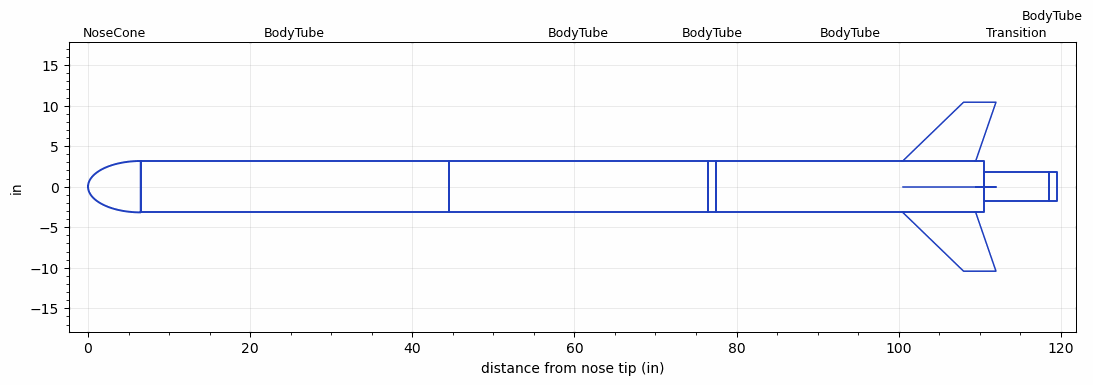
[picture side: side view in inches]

<RASAeroDocument>
 <FileVersion>2</FileVersion>
 <RocketDesign>
  <NoseCone>
   <Length>6.5</Length>
   <Diameter>6.34</Diameter>
   <Shape>Elliptical</Shape>
   <Location>0</Location>
  </NoseCone>
  <BodyTube>
   <Length>38</Length>
   <Diameter>6.34</Diameter>
   <Location>6.5</Location>
  </BodyTube>
  <BodyTube>
   <Length>32</Length>
   <Diameter>6.34</Diameter>
   <Location>44.5</Location>
  </BodyTube>
  <BodyTube>
   <Length>1</Length>
   <Diameter>6.34</Diameter>
   <Location>76.5</Location>
  </BodyTube>
  <BodyTube>
   <Length>33</Length>
   <Diameter>6.34</Diameter>
   <RailGuideDiameter>0.49</RailGuideDiameter>
   <RailGuideHeight>0.187</RailGuideHeight>
   <Location>77.5</Location>
   <Fin>
    <Count>4</Count>
    <Chord>9</Chord>
    <Span>7.25</Span>
    <SweepDistance>7.5</SweepDistance>
    <TipChord>4</TipChord>
    <Thickness>0.125</Thickness>
    <Location>10</Location>
    <AirfoilSection>Square</AirfoilSection>
   </Fin>
   <Protuberance>
    <StreamlinedNoBaseDrag>7</StreamlinedNoBaseDrag>
    <StreamlinedWithBaseDrag>0</StreamlinedWithBaseDrag>
    <InclinedPlate1Angle>0</InclinedPlate1Angle>
    <InclinedPlate1FrontalArea>0</InclinedPlate1FrontalArea>
    <InclinedPlate2Angle>0</InclinedPlate2Angle>
    <InclinedPlate2FrontalArea>0</InclinedPlate2FrontalArea>
   </Protuberance>
  </BodyTube>
  <Transition>
   <Length>8</Length>
   <Diameter>3.65</Diameter>
   <Location>110.5</Location>
   <RearDiameter>3.65</RearDiameter>
  </Transition>
  <BodyTube>
   <Length>1</Length>
   <Diameter>3.65</Diameter>
   <Location>118.5</Location>
  </BodyTube>
  <Surface>Rough Camouflage Paint</Surface>
  <ModifiedBarrowman>False</ModifiedBarrowman>
  <Turbulence>False</Turbulence>
  <UseBooster1>False</UseBooster1>
  <UseBooster2>False</UseBooster2>
 </RocketDesign>
 <LaunchSite>
  <Altitude>0</Altitude>
  <Pressure>0</Pressure>
  <RodAngle>10</RodAngle>
  <RodLength>10</RodLength>
  <Temperature>74</Temperature>
  <WindSpeed>20</WindSpeed>
 </LaunchSite>
 <Recovery>
  <Altitude1>1000</Altitude1>
  <Altitude2>800</Altitude2>
  <DeviceType1>Parachute</DeviceType1>
  <DeviceType2>Parachute</DeviceType2>
  <Event1>True</Event1>
  <Event2>True</Event2>
  <Size1>18</Size1>
  <Size2>96</Size2>
  <EventType1>Apogee</EventType1>
  <EventType2>Altitude</EventType2>
  <CD1>1.55</CD1>
  <CD2>2.2</CD2>
 </Recovery>
 <SimulationList>
  <Simulation>
   <SustainerEngine>L1390G  (AT)</SustainerEngine>
   <SustainerLaunchWt>42.3</SustainerLaunchWt>
   <SustainerNozzleDiameter>1</SustainerNozzleDiameter>
   <SustainerCG>71.85</SustainerCG>
   <SustainerIgnitionDelay>0</SustainerIgnitionDelay>
   <Booster1SeparationDelay>0</Booster1SeparationDelay>
   <Booster1IgnitionDelay>0</Booster1IgnitionDelay>
   <IncludeBooster1>False</IncludeBooster1>
   <Booster2Delay>0</Booster2Delay>
   <IncludeBooster2>False</IncludeBooster2>
   <TimetoApogee>16.11027</TimetoApogee>
   <MaxAltitude>4017.557</MaxAltitude>
   <MaxVelocity>596.4692</MaxVelocity>
  </Simulation>
 </SimulationList>
</RASAeroDocument>
